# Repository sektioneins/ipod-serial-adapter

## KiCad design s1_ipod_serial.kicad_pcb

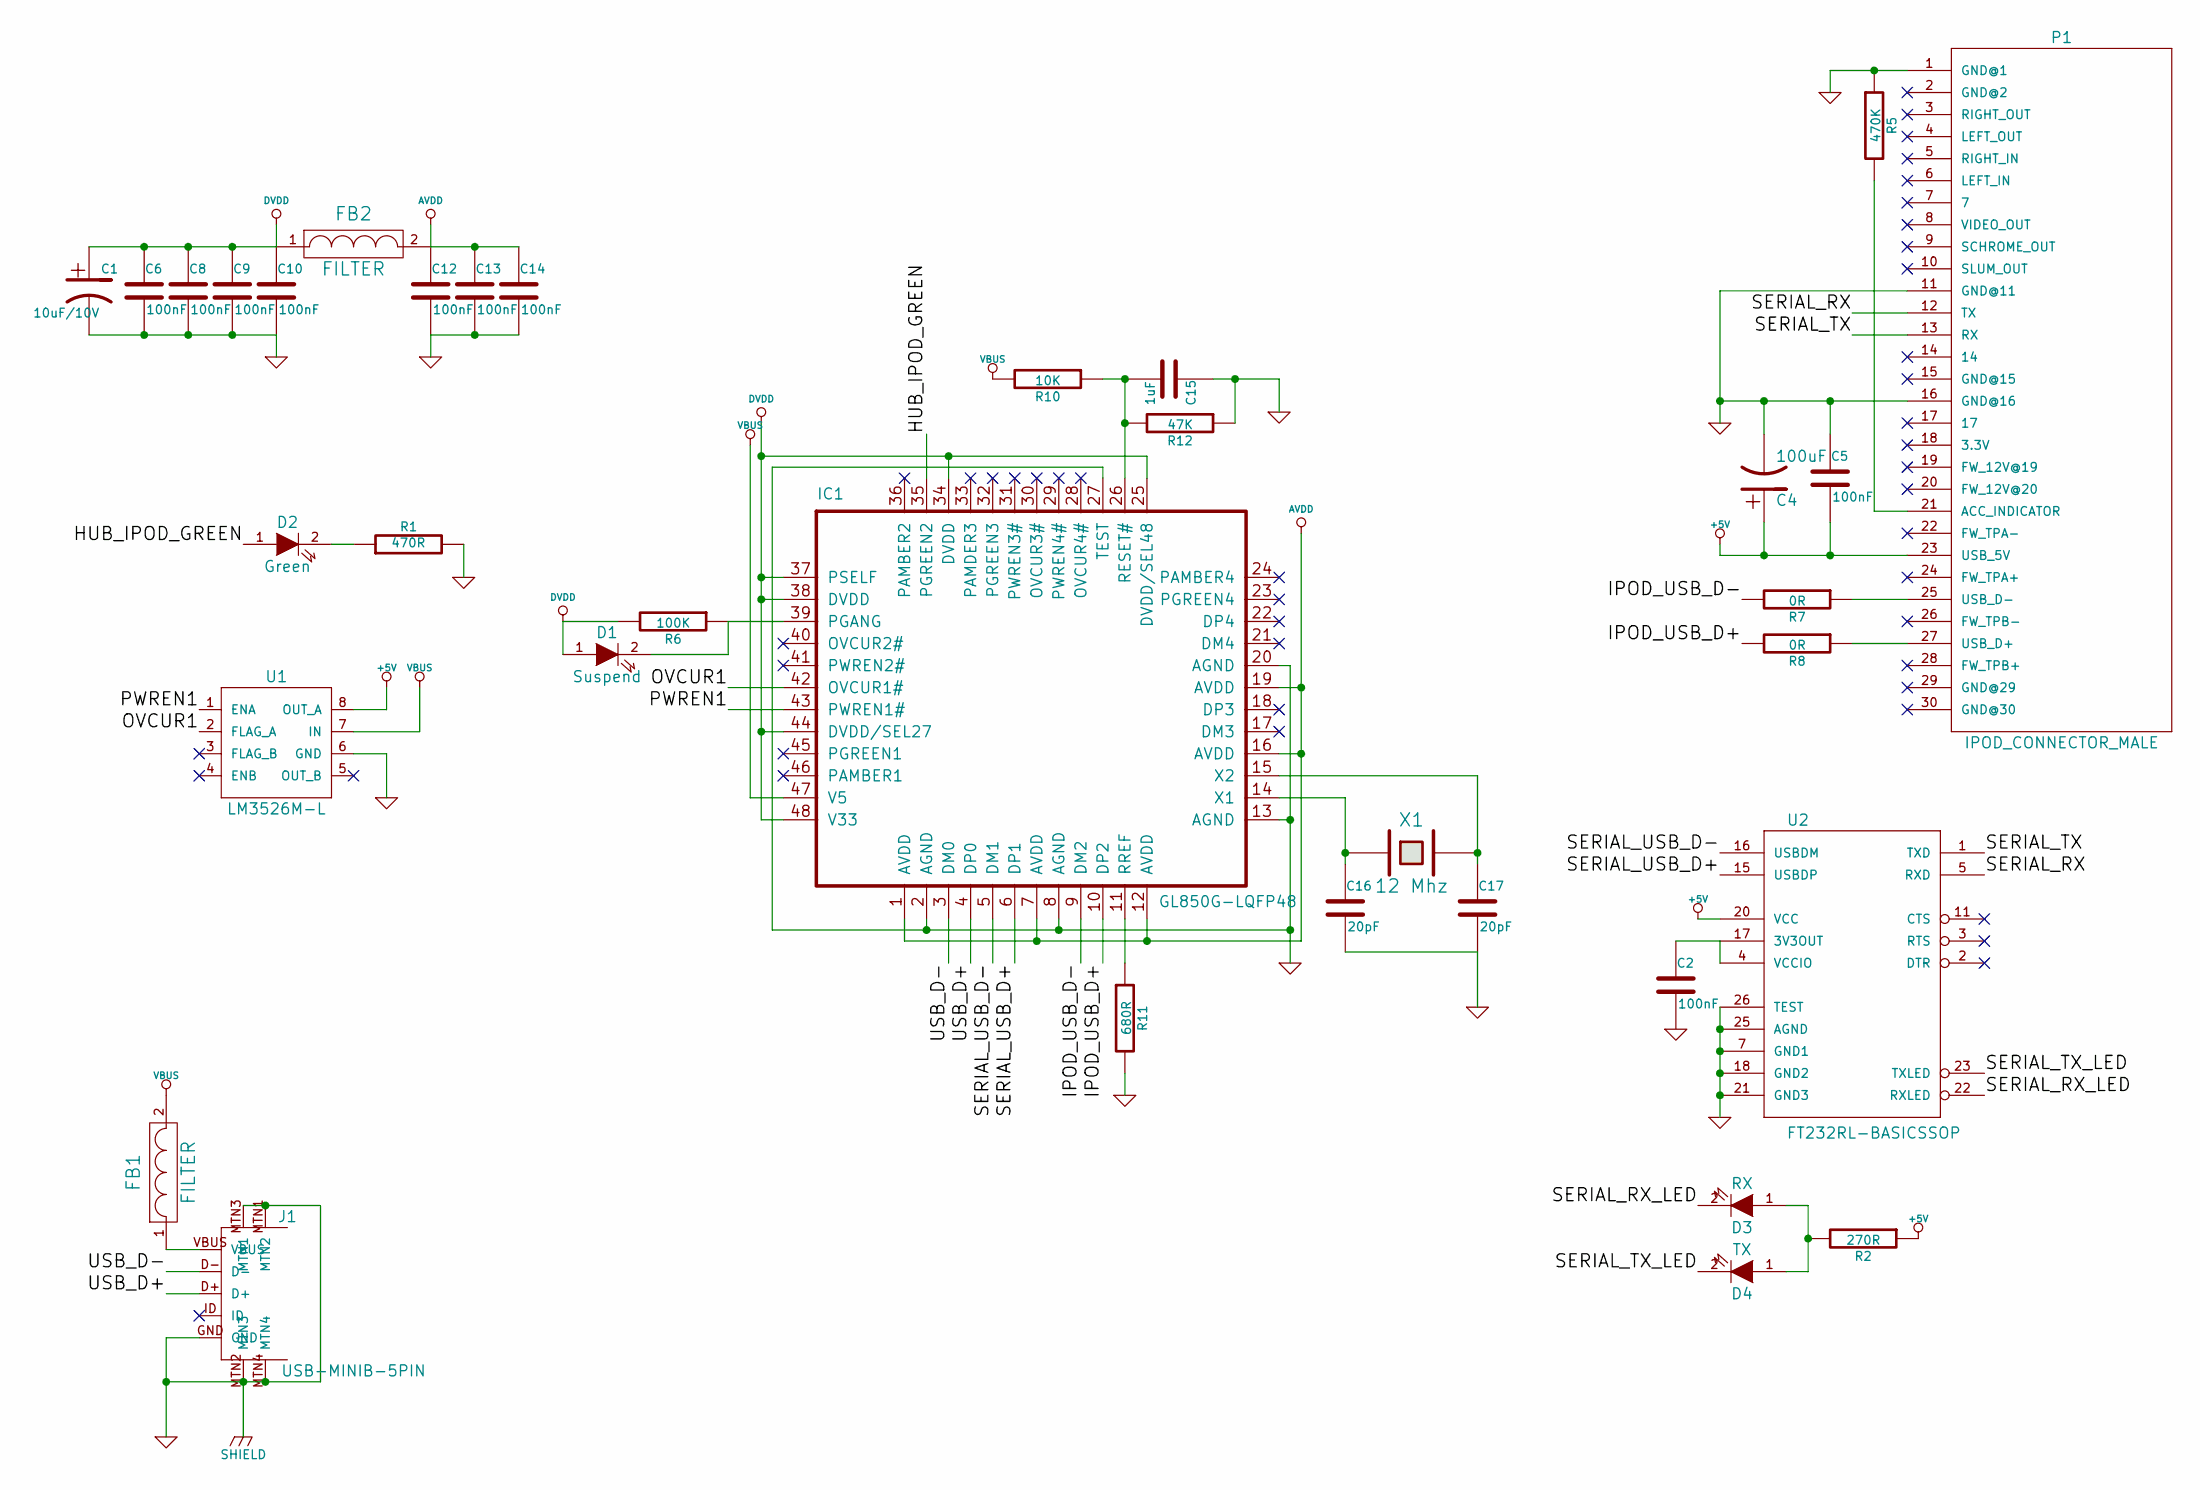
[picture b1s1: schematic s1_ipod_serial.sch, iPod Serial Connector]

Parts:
C1: 10uF/10V
C2, C5, C6, C8, C9, C10, C12, C13, C14: 100nF
C4: 100uF
C15: 1uF
C16, C17: 20pF
D1: Suspend
D2: Green
D3: RX
D4: TX
FB1, FB2: FILTER
IC1: GL850G-LQFP48; ElevenDroids - ICs-SSOP28
J1: USB-MINIB-5PIN
P1: IPOD_CONNECTOR_MALE
R1: 470R
R2: 270R
R5: 470K
R6: 100K
R7, R8: 0R
R10: 10K
R11: 680R
R12: 47K
U1: LM3526M-L
U2: FT232RL-BASICSSOP; SparkFun-SSOP28DB
X1: 12 Mhz

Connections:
+5V: C4.1, C5.2, P1.23 (USB_5V), R2.1, U1.8 (OUT_A), U2.20 (VCC)
/HUB_IPOD_GREEN: D2.1 (A), IC1.35 (PGREEN2)
/IPOD_USB_D+: IC1.10 (DP2), R8.2
/IPOD_USB_D-: IC1.9 (DM2), R7.2
/OVCUR1: IC1.42 (OVCUR1#), U1.2 (FLAG_A)
/PWREN1: IC1.43 (PWREN1#), U1.1 (ENA)
/SERIAL_RX: P1.12 (TX), U2.5 (RXD)
/SERIAL_RX_LED: D3.2 (K), U2.22 (RXLED)
/SERIAL_TX: P1.13 (RX), U2.1 (TXD)
/SERIAL_TX_LED: D4.2 (K), U2.23 (TXLED)
/SERIAL_USB_D+: IC1.6 (DP1), U2.15 (USBDP)
/SERIAL_USB_D-: IC1.5 (DM1), U2.16 (USBDM)
/USB_D+: IC1.4 (DP0), J1.D+
/USB_D-: IC1.3 (DM0), J1.D-
AVDD: C12.1, C13.1, C14.1, FB2.2, IC1.1 (AVDD), IC1.7 (AVDD), IC1.12 (AVDD), IC1.16 (AVDD), IC1.19 (AVDD)
DVDD: C1.1, C6.1, C8.1, C9.1, C10.1, D1.1 (A), FB2.1, IC1.25 (DVDD/SEL48), IC1.34 (DVDD), IC1.37 (PSELF), IC1.38 (DVDD), IC1.44 (DVDD/SEL27), IC1.48 (V33), R6.2
GND: C1.2, C2.2, C4.2, C5.1, C6.2, C8.2, C9.2, C10.2, C12.2, C13.2, C14.2, C15.1, C16.2, C17.2, IC1.2 (AGND), IC1.8 (AGND), IC1.13 (AGND), IC1.20 (AGND), IC1.27 (TEST), J1.GND, J1.MTN1 (MTN2), J1.MTN2 (MTN3), J1.MTN3 (MTN1), J1.MTN4, P1.1 (GND@1), P1.11 (GND@11), P1.16 (GND@16), R1.2, R5.1, R11.2, R12.1, U1.6 (GND), U2.7 (GND1), U2.18 (GND2), U2.21 (GND3), U2.25 (AGND), U2.26 (TEST)
unnamed: C2.1, U2.4 (VCCIO), U2.17 (3V3OUT)
unnamed: C15.2, IC1.26 (RESET#), R10.1, R12.2
unnamed: C16.1, IC1.14 (X1), X1.1
unnamed: C17.1, IC1.15 (X2), X1.2
unnamed: D1.2 (K), IC1.39 (PGANG), R6.1
unnamed: D2.2 (K), R1.1
unnamed: D3.1 (A), D4.1 (A), R2.2
unnamed: FB1.1, J1.VBUS
unnamed: IC1.11 (RREF), R11.1
unnamed: P1.21 (ACC_INDICATOR), R5.2
unnamed: P1.25 (USB_D-), R7.1
unnamed: P1.27 (USB_D+), R8.1
VBUS: FB1.2, IC1.47 (V5), R10.2, U1.7 (IN)

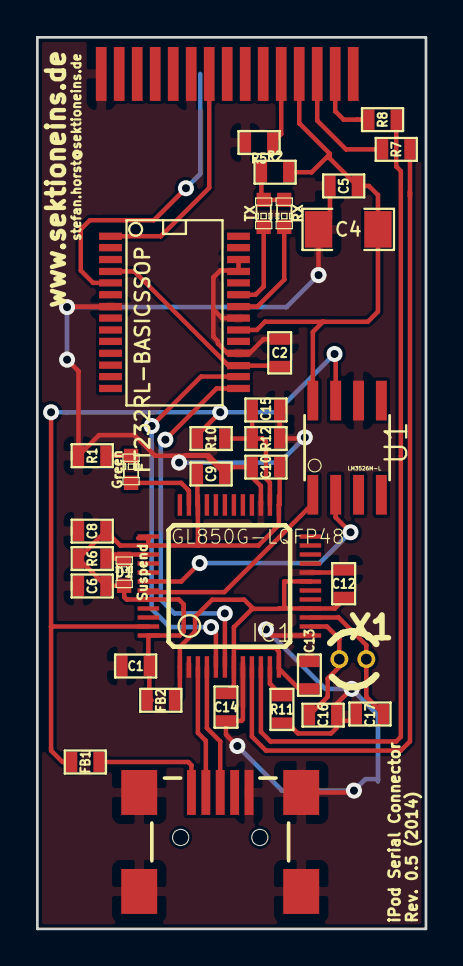
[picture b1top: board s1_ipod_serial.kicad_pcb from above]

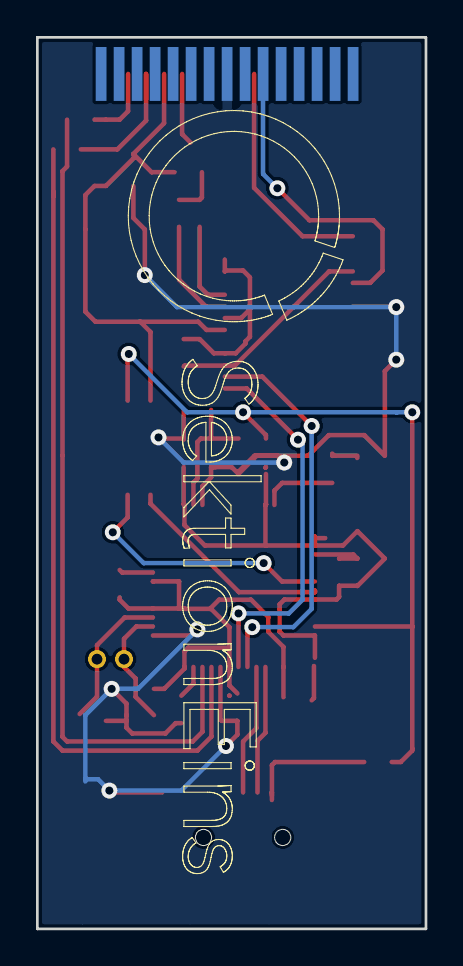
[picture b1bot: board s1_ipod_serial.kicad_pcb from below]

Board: 2 copper layers, 21.6 x 49.5 mm, 36 parts (2 on the bottom side), 30 nets.

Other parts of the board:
SektionEinsLogo: VAL**; SektionEinsLogo

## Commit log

2014-04-23 init
2014-04-23 added gitignore
2014-06-04 new routing for usb, teileliste added, fix for selfpowered
2014-06-04 added digikey article numbers to teileliste
2014-06-04 added some teile
2014-06-06 removed the 0R for self powered indicator, made fb 0608, rev. text added to board and sheet, routing optimized
2014-07-07 kondensatoren sind jetzt smd
2016-12-01 added current version
